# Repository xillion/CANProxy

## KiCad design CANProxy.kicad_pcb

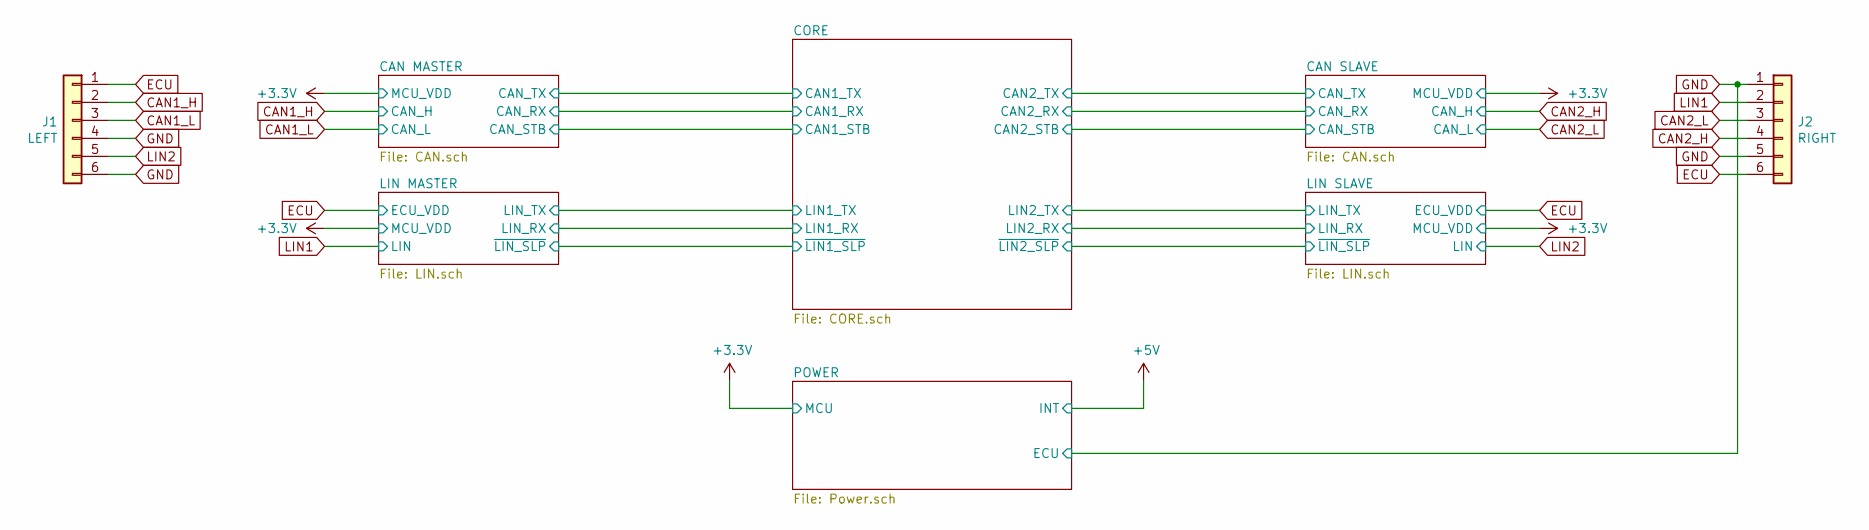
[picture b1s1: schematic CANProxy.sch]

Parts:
J1: LEFT; Wago_734-166_1x06_P3.50mm_Horizontal; PartNumber ULO-TB01-15RC/3.5-06P-4
J2: RIGHT; Wago_734-166_1x06_P3.50mm_Horizontal; PartNumber ULO-TB01-15RC/3.5-06P-4

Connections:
CAN1_H: J1.2; also elsewhere on the board
CAN1_L: J1.3; also elsewhere on the board
CAN2_H: J2.4; also elsewhere on the board
CAN2_L: J2.3; also elsewhere on the board
ECU: J1.1, J2.6; also elsewhere on the board
GND: J1.4, J1.6, J2.1, J2.5; also elsewhere on the board
LIN1: J2.2; also elsewhere on the board
LIN2: J1.5; also elsewhere on the board

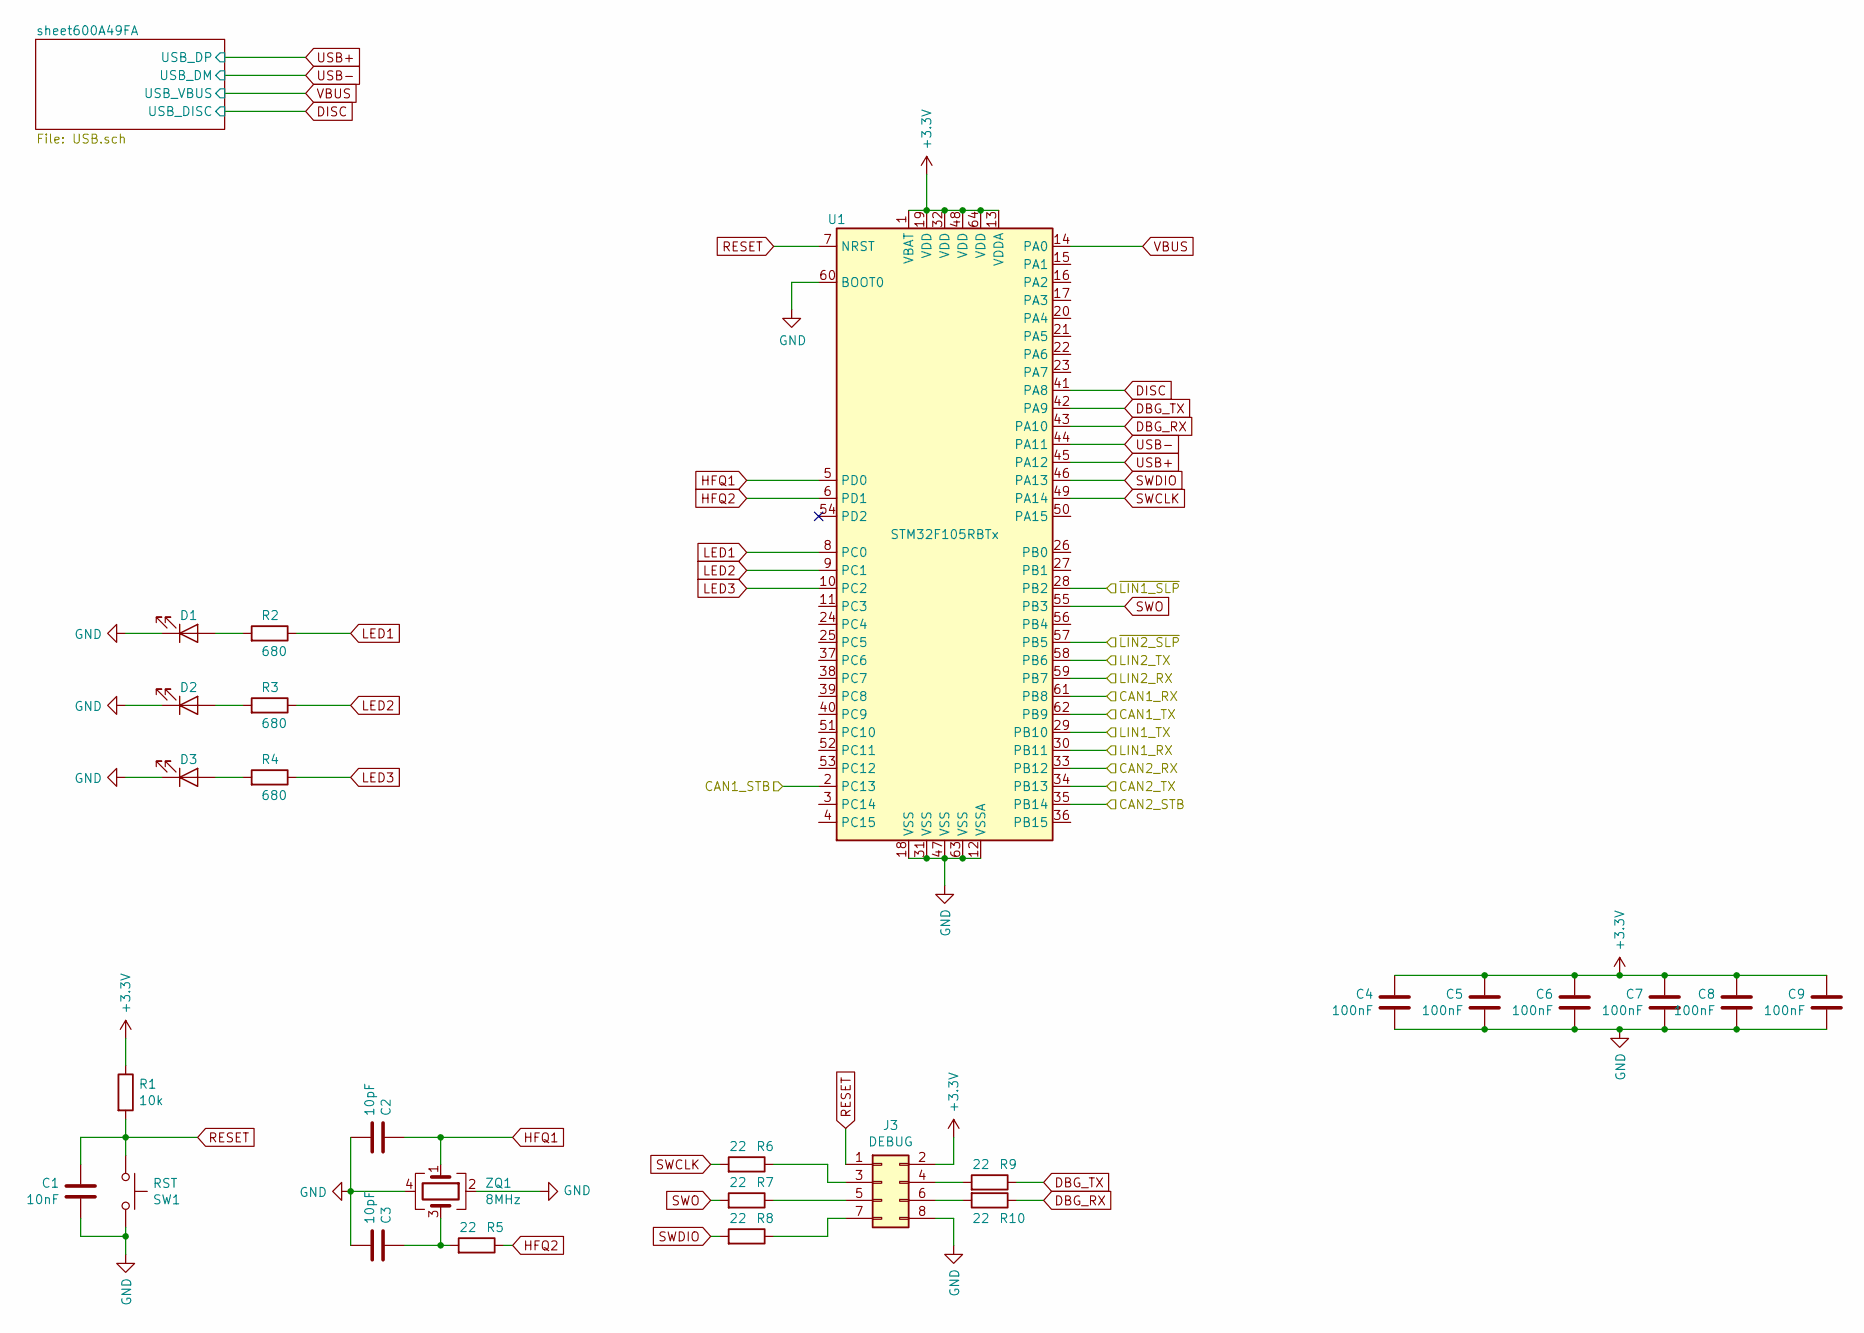
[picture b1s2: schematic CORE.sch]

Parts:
C1: 10nF; C_0805_2012Metric; PartNumber CL31B103KBCNNNC
C2, C3: 10pF; C_0603_1608Metric; PartNumber CL10C100JB8NNNC
C4, C5, C6, C7, C8, C9: 100nF; C_0603_1608Metric; PartNumber CL10B104KC8NNNC
D1: LED GREEN; LED_0805_2012Metric; PartNumber LTST-C170KGKT
D2: LED RED; LED_0805_2012Metric; PartNumber LTST-C170KRKT
D3: LED ORANGE; LED_0805_2012Metric; PartNumber LTST-C171KFKT
J3: DEBUG; PinHeader_2x04_P2.00mm_Vertical; PartNumber MTP220-1204S1
R1: 10k; R_0603_1608Metric; PartNumber RC0603JR-0710KL
R2, R3, R4: 680; R_0603_1608Metric; PartNumber RC0603FR-07680RL
R5, R6, R7, R8, R9, R10: 22; R_0603_1608Metric; PartNumber RC0603FR-0722RL
SW1: RST; SW_SPST_B3U-3000P; PartNumber SKRELGE010
U1: STM32F105RBTx; LQFP-64_10x10mm_P0.5mm; PartNumber STM32F105RBT6
ZQ1: 8MHz; Crystal_SMD_3225-4Pin_3.2x2.5mm; PartNumber 7V12000005

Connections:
+3V3: C4.1, C5.1, C6.1, C7.1, C8.1, C9.1, J3.2, R1.1, U1.1 (VBAT), U1.13 (VDDA), U1.19 (VDD), U1.32 (VDD), U1.48 (VDD), U1.64 (VDD); also elsewhere on the board
/CORE/CAN1_RX: U1.61 (PB8); also elsewhere on the board
/CORE/CAN1_STB: U1.2 (PC13); also elsewhere on the board
/CORE/CAN1_TX: U1.62 (PB9); also elsewhere on the board
/CORE/CAN2_RX: U1.33 (PB12); also elsewhere on the board
/CORE/CAN2_STB: U1.35 (PB14); also elsewhere on the board
/CORE/CAN2_TX: U1.34 (PB13); also elsewhere on the board
/CORE/LIN1_RX: U1.30 (PB11); also elsewhere on the board
/CORE/LIN1_TX: U1.29 (PB10); also elsewhere on the board
/CORE/LIN2_RX: U1.59 (PB7); also elsewhere on the board
/CORE/LIN2_TX: U1.58 (PB6); also elsewhere on the board
/CORE/~LIN1_SLP: U1.28 (PB2); also elsewhere on the board
/CORE/~LIN2_SLP: U1.57 (PB5); also elsewhere on the board
DBG_RX: R10.1, U1.43 (PA10)
DBG_TX: R9.1, U1.42 (PA9)
DISC: U1.41 (PA8); also elsewhere on the board
GND: C1.2, C2.2, C3.2, C4.2, C5.2, C6.2, C7.2, C8.2, C9.2, D1.1 (K), D2.1 (K), D3.1 (K), J3.8, SW1.1, U1.12 (VSSA), U1.18 (VSS), U1.31 (VSS), U1.47 (VSS), U1.60 (BOOT0), U1.63 (VSS), ZQ1.2, ZQ1.4; also elsewhere on the board
HFQ1: C2.1, U1.5 (PD0), ZQ1.1
HFQ2: R5.1, U1.6 (PD1)
LED1: R2.1, U1.8 (PC0)
LED2: R3.1, U1.9 (PC1)
LED3: R4.1, U1.10 (PC2)
unnamed: C3.1, R5.2, ZQ1.3
unnamed: D1.2 (A), R2.2
unnamed: D2.2 (A), R3.2
unnamed: D3.2 (A), R4.2
unnamed: J3.3, R6.1
unnamed: J3.4, R9.2
unnamed: J3.5, R7.1
unnamed: J3.6, R10.2
unnamed: J3.7, R8.1
RESET: C1.1, J3.1, R1.2, SW1.2, U1.7 (NRST)
SWCLK: R6.2, U1.49 (PA14)
SWDIO: R8.2, U1.46 (PA13)
SWO: R7.2, U1.55 (PB3)
USB+: U1.45 (PA12); also elsewhere on the board
USB-: U1.44 (PA11); also elsewhere on the board
VBUS: U1.14 (PA0); also elsewhere on the board

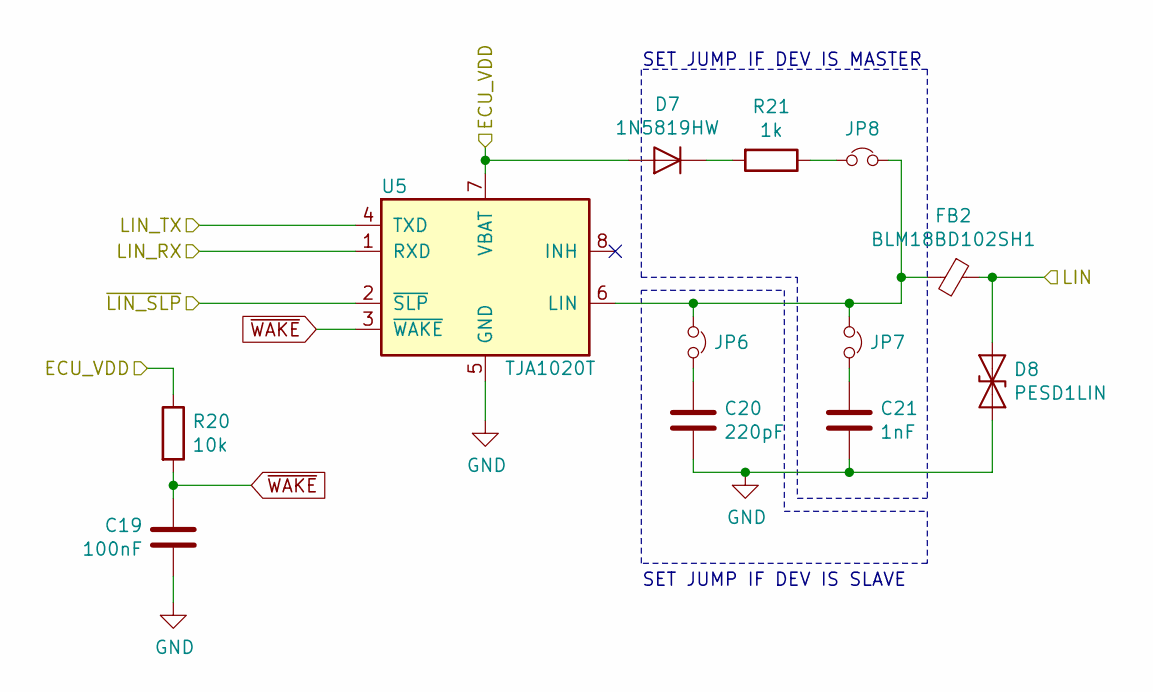
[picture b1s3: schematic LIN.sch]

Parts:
C13: 100nF; C_0603_1608Metric; PartNumber CL10B104KC8NNNC
C14: 220pF; C_0603_1608Metric; PartNumber CL10B221KB8NNNC
C15: 1nF; C_0603_1608Metric; PartNumber CL10B102KB8NNNC
D4: 1N5819HW; D_SOD-123; PartNumber 1N5819HW-7-F
D8: PESD1LIN; D_SOD-323; PartNumber PESD1LIN,115
FB2: BLM18BD102SH1; L_0603_1608Metric; PartNumber BLM18BD102SH1D
JP1, JP2, JP3: Jumper_NC_Small; SolderJumper-2_P1.3mm_Open_RoundedPad1.0x1.5mm; PartNumber NOT A COMPONENT
R16: 10k; R_0603_1608Metric; PartNumber RC0603JR-0710KL
R17: 1k; R_0805_2012Metric; PartNumber RC0603FR-071KL
U3: TJA1020T; SOIC-8_3.9x4.9mm_P1.27mm; PartNumber TJA1020T/CM,118

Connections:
/CORE/LIN1_RX: U3.1 (RXD); also elsewhere on the board
/CORE/LIN1_TX: U3.4 (TXD); also elsewhere on the board
/CORE/~LIN1_SLP: U3.2 (~SLP~); also elsewhere on the board
ECU: D4.2 (A), R16.1, U3.7 (VBAT); also elsewhere on the board
GND: C13.2, C14.2, C15.2, D8.2 (A2), U3.5 (GND); also elsewhere on the board
LIN2: D8.1 (A1), FB2.1; also elsewhere on the board
unnamed: C14.1, JP1.2
unnamed: C15.1, JP2.2
unnamed: D4.1 (K), R17.2
unnamed: JP3.1, R17.1
~WAKE: C13.1, R16.2, U3.3 (~WAKE~); also elsewhere on the board

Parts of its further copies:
C19: 100nF; C_0603_1608Metric; PartNumber CL10B104KC8NNNC
C20: 220pF; C_0603_1608Metric; PartNumber CL10B221KB8NNNC
C21: 1nF; C_0603_1608Metric; PartNumber CL10B102KB8NNNC
D5: PESD1LIN; D_SOD-323; PartNumber PESD1LIN,115
D7: 1N5819HW; D_SOD-123; PartNumber 1N5819HW-7-F
FB1: BLM18BD102SH1; L_0603_1608Metric; PartNumber BLM18BD102SH1D
JP6, JP7, JP8: Jumper_NC_Small; SolderJumper-2_P1.3mm_Open_RoundedPad1.0x1.5mm; PartNumber NOT A COMPONENT
R20: 10k; R_0603_1608Metric; PartNumber RC0603JR-0710KL
R21: 1k; R_0805_2012Metric; PartNumber RC0603FR-071KL
U5: TJA1020T; SOIC-8_3.9x4.9mm_P1.27mm; PartNumber TJA1020T/CM,118

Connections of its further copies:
/CORE/LIN2_RX: U5.1 (RXD); also elsewhere on the board
/CORE/LIN2_TX: U5.4 (TXD); also elsewhere on the board
/CORE/~LIN2_SLP: U5.2 (~SLP~); also elsewhere on the board
ECU: D7.2 (A), R20.1, U5.7 (VBAT); also elsewhere on the board
GND: C19.2, C20.2, C21.2, D5.2 (A2), U5.5 (GND); also elsewhere on the board
LIN1: D5.1 (A1), FB1.1; also elsewhere on the board
unnamed: C20.1, JP6.2
unnamed: C21.1, JP7.2
unnamed: D7.1 (K), R21.2
unnamed: JP8.1, R21.1
~WAKE: C19.1, R20.2, U5.3 (~WAKE~); also elsewhere on the board

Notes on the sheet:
SET JUMP IF DEV IS MASTER
SET JUMP IF DEV IS SLAVE

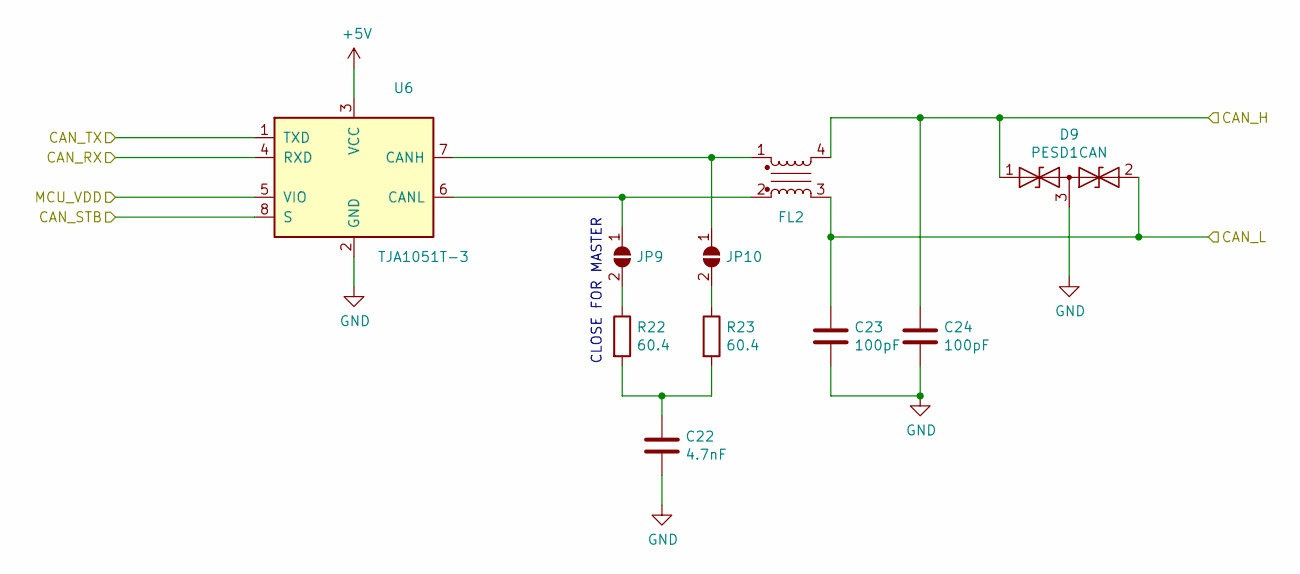
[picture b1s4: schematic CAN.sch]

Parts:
C16: 4.7nF; C_0603_1608Metric; PartNumber CL21B472KBANNNC
C17, C18: 100pF; C_0603_1608Metric; PartNumber CL10B101KB8NNNC
D6: PESD1CAN; SOT-23; PartNumber PESD1CAN,215
FL1: ACT45B-510-2P-TL003; Filter_TDK_ACT45B_4.5x3.2mm; PartNumber ACT45B-510-2P-TL003
JP4, JP5: SolderJumper_2_Open; SolderJumper-2_P1.3mm_Open_RoundedPad1.0x1.5mm; PartNumber NOT A COMPONENT
R18, R19: 60.4; R_0805_2012Metric; PartNumber RC0603FR-0760R4L
U4: TJA1051T-3; SOIC-8_3.9x4.9mm_P1.27mm; PartNumber TJA1051T/3/1J

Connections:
+3V3: U4.5 (VIO); also elsewhere on the board
+5V: U4.3 (VCC); also elsewhere on the board
/CORE/CAN1_RX: U4.4 (RXD); also elsewhere on the board
/CORE/CAN1_STB: U4.8 (S); also elsewhere on the board
/CORE/CAN1_TX: U4.1 (TXD); also elsewhere on the board
CAN1_H: C18.1, D6.1 (A1), FL1.4; also elsewhere on the board
CAN1_L: C17.1, D6.2 (A2), FL1.3; also elsewhere on the board
GND: C16.2, C17.2, C18.2, D6.3 (common), U4.2 (GND); also elsewhere on the board
unnamed: C16.1, R18.2, R19.2
unnamed: FL1.1, JP5.1 (A), U4.7 (CANH)
unnamed: FL1.2, JP4.1 (A), U4.6 (CANL)
unnamed: JP4.2 (B), R18.1
unnamed: JP5.2 (B), R19.1

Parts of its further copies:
C22: 4.7nF; C_0603_1608Metric; PartNumber CL21B472KBANNNC
C23, C24: 100pF; C_0603_1608Metric; PartNumber CL10B101KB8NNNC
D9: PESD1CAN; SOT-23; PartNumber PESD1CAN,215
FL2: ACT45B-510-2P-TL003; Filter_TDK_ACT45B_4.5x3.2mm; PartNumber ACT45B-510-2P-TL003
JP9, JP10: SolderJumper_2_Open; SolderJumper-2_P1.3mm_Open_RoundedPad1.0x1.5mm; PartNumber NOT A COMPONENT
R22, R23: 60.4; R_0805_2012Metric; PartNumber RC0603FR-0760R4L
U6: TJA1051T-3; SOIC-8_3.9x4.9mm_P1.27mm; PartNumber TJA1051T/3/1J

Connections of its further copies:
+3V3: U6.5 (VIO); also elsewhere on the board
+5V: U6.3 (VCC); also elsewhere on the board
/CORE/CAN2_RX: U6.4 (RXD); also elsewhere on the board
/CORE/CAN2_STB: U6.8 (S); also elsewhere on the board
/CORE/CAN2_TX: U6.1 (TXD); also elsewhere on the board
CAN2_H: C24.1, D9.1 (A1), FL2.4; also elsewhere on the board
CAN2_L: C23.1, D9.2 (A2), FL2.3; also elsewhere on the board
GND: C22.2, C23.2, C24.2, D9.3 (common), U6.2 (GND); also elsewhere on the board
unnamed: C22.1, R22.2, R23.2
unnamed: FL2.1, JP10.1 (A), U6.7 (CANH)
unnamed: FL2.2, JP9.1 (A), U6.6 (CANL)
unnamed: JP9.2 (B), R22.1
unnamed: JP10.2 (B), R23.1

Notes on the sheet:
CLOSE FOR MASTER

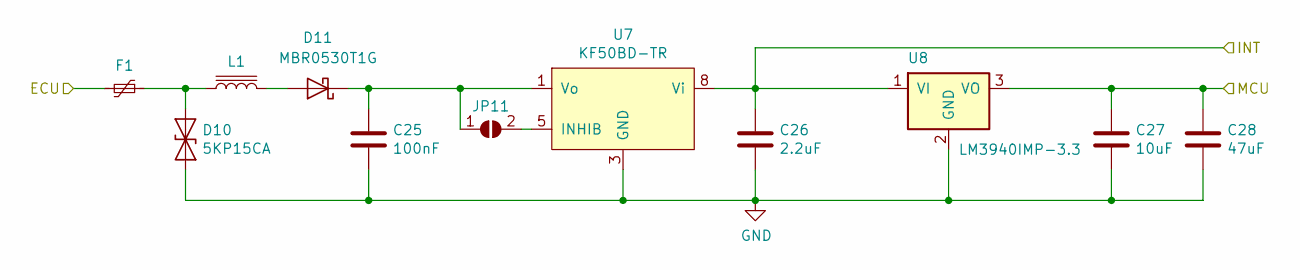
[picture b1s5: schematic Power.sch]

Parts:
C25: 100nF; C_0603_1608Metric; PartNumber CL10B104KC8NNNC
C26: 2.2uF; C_0805_2012Metric; PartNumber CL21F225ZPFNNNE
C27: 10uF; C_0805_2012Metric; PartNumber CL21A106KPFNNNE
C28: 47uF; C_0805_2012Metric; PartNumber CL21A476MQYNNNE
D10: 5KP15CA; D_5KP_P10.16mm_Horizontal
D11: MBR0530T1G; D_SOD-123; PartNumber MBR0530T1G
F1: 1206L025YR; Fuse_1206_3216Metric; PartNumber 1206L025YR
JP11: SolderJumper_2_Open; SolderJumper-2_P1.3mm_Open_RoundedPad1.0x1.5mm; PartNumber NOT A COMPONENT
L1: L_Core_Iron; L_1206_3216Metric
U7: KF50BD-TR; SO-8_3.9x4.9mm_P1.27mm; PartNumber KF50BD-TR
U8: LM3940IMP-3.3; SOT-223-3_TabPin2; PartNumber LM3940IMP-3.3/NOPB

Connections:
+3V3: C27.1, C28.1, U8.3 (VO); also elsewhere on the board
+5V: C26.1, U7.8 (Vi), U8.1 (VI); also elsewhere on the board
GND: C25.2, C26.2, C27.2, C28.2, D10.2 (A2), F1.2, U7.2 (GND), U7.3 (GND), U7.4 (NC), U7.6 (GND), U7.7 (GND), U8.2 (GND); also elsewhere on the board
unnamed: C25.1, D11.1 (K), JP11.1 (A), U7.1 (Vo)
unnamed: D10.1 (A1), F1.1, L1.1
unnamed: D11.2 (A), L1.2
unnamed: JP11.2 (B), U7.5 (INHIB)

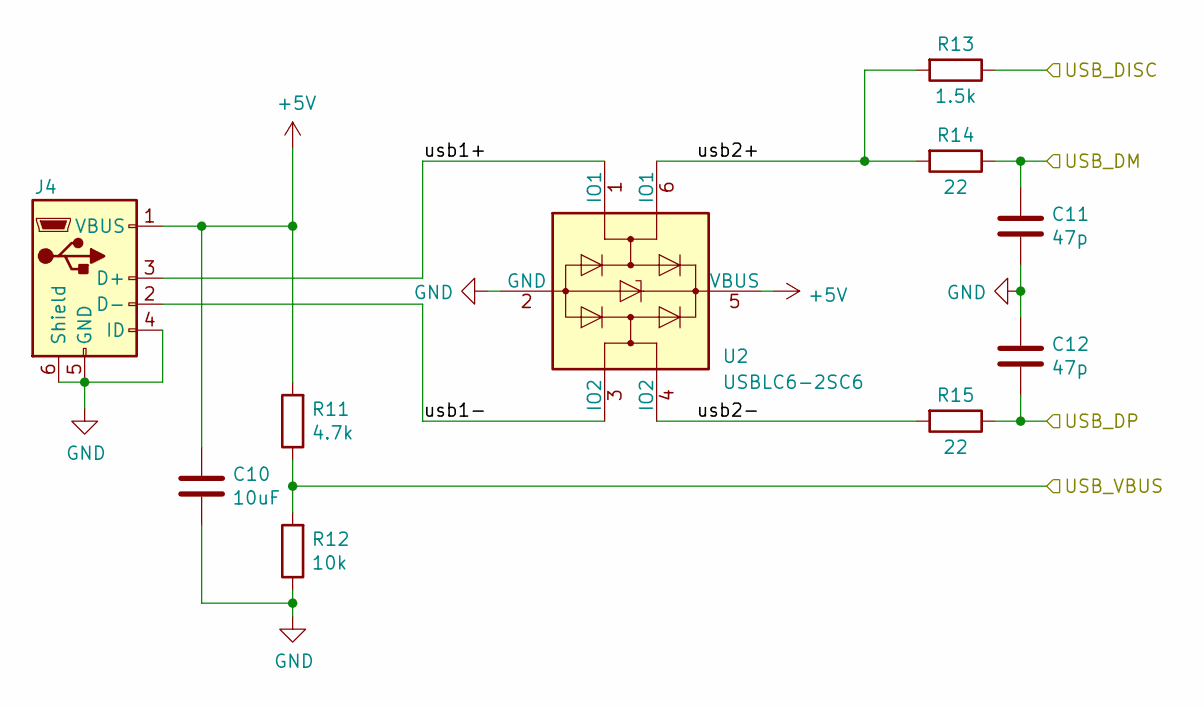
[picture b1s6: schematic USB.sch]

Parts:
C10: 10uF; C_0805_2012Metric; PartNumber CL21A106KPFNNNE
C11, C12: 47p; C_0603_1608Metric; PartNumber CL10C470KB8NNNC
J4: USB_B_Micro; USB_Micro-B_GCT_USB3076-30-A
R11: 4.7k; R_0603_1608Metric; PartNumber RC0603FR-074K7L
R12: 10k; R_0603_1608Metric; PartNumber RC0603JR-0710KL
R13: 1.5k; R_0603_1608Metric; PartNumber RC0603FR-071K5L
R14, R15: 22; R_0603_1608Metric; PartNumber RC0603FR-0722RL
U2: USBLC6-2SC6; SOT-23-6; PartNumber USBLC6-2SC6

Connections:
+5V: C10.1, J4.1 (VBUS), R11.2, U2.5 (VBUS); also elsewhere on the board
/CORE/sheet600A49FA/usb1+: J4.3 (D+), U2.1 (IO1)
/CORE/sheet600A49FA/usb1-: J4.2 (D-), U2.3 (IO2)
/CORE/sheet600A49FA/usb2+: R13.2, R14.2, U2.6 (IO1)
/CORE/sheet600A49FA/usb2-: R15.2, U2.4 (IO2)
DISC: R13.1; also elsewhere on the board
GND: C10.2, C11.2, C12.1, J4.4 (ID), J4.5 (GND), J4.6 (Shield), R12.1, U2.2 (GND); also elsewhere on the board
USB+: C12.2, R15.1; also elsewhere on the board
USB-: C11.1, R14.1; also elsewhere on the board
VBUS: R11.1, R12.2; also elsewhere on the board

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
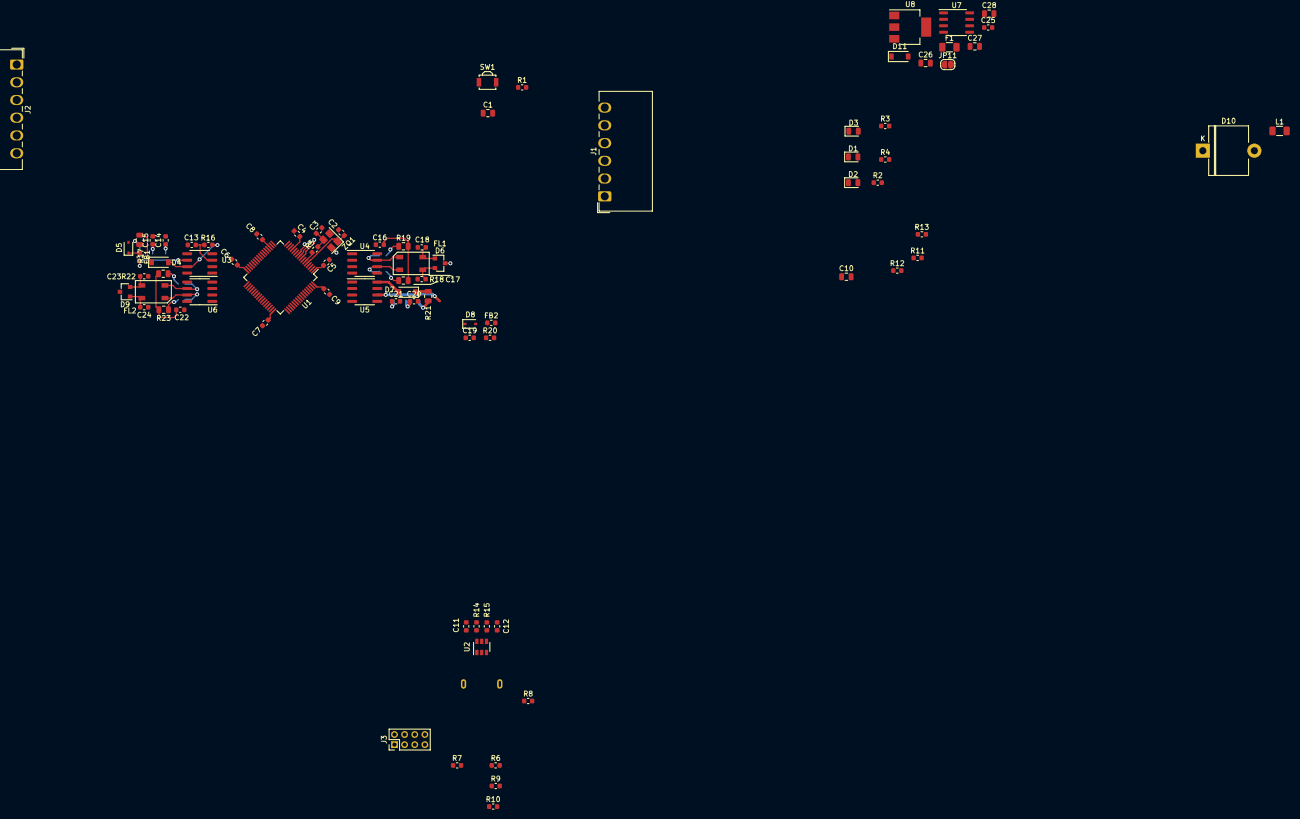
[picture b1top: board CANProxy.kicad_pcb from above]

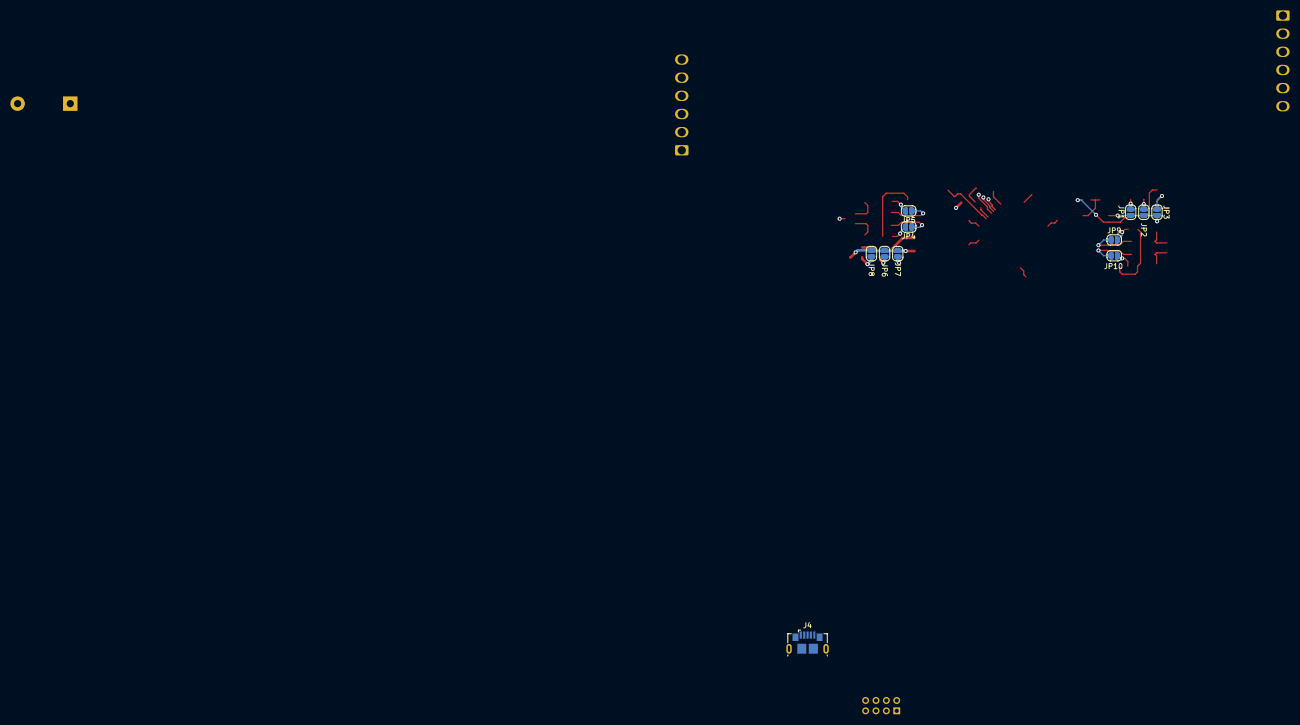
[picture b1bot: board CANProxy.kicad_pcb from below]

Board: 2 copper layers, 93 parts (11 on the bottom side), 75 nets.

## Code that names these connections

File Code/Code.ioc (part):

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PD1-OSC_OUT.Mode=HSE-External-Oscillator
Mcu.UserName=STM32F105RBTx
PC10.Signal=UART4_TX
PC11.Signal=UART4_RX
PC10.Mode=Asynchronous
PA11.Mode=Device_Only
PD0-OSC_IN.Signal=RCC_OSC_IN
PB13.Signal=CAN2_TX
PD1-OSC_OUT.Signal=RCC_OSC_OUT
PA13.Signal=SYS_JTMS-SWDIO
PA3.Mode=LIN
PA9.Mode=Activate_VBUS
PA12.Signal=USB_OTG_FS_DP
PB9.Mode=CAN_Activate
PA9.Signal=USB_OTG_FS_VBUS
PB6.Signal=USART1_TX
PB6.Mode=LIN
PD0-OSC_IN.Mode=HSE-External-Oscillator
PB3.Mode=Trace_Asynchronous_SW
board=custom
PA14.Mode=Trace_Asynchronous_SW
PB7.Signal=USART1_RX
PA8.Signal=USB_OTG_FS_SOF
PA13.Mode=Trace_Asynchronous_SW
Mcu.Name=STM32F105R(8-B-C)Tx
PA2.Signal=USART2_TX
PB3.Signal=SYS_TRACESWO
Mcu.Package=LQFP64
PB9.Signal=CAN1_TX
PB12.Mode=CAN_Activate
PA12.Mode=Device_Only
PB7.Mode=LIN
PA11.Signal=USB_OTG_FS_DM
PA14.Signal=SYS_JTCK-SWCLK
PC11.Mode=Asynchronous
PB8.Mode=CAN_Activate
PA2.Mode=LIN
PB8.Signal=CAN1_RX
PA8.Mode=Activate_SOF_FS
PB13.Mode=CAN_Activate
PB12.Signal=CAN2_RX
PA3.Signal=USART2_RX

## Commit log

2021-01-24 corrected CAN schematic
2021-01-25 Start routing
2021-01-27 CAN part routing
